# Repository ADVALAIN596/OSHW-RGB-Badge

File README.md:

# OSHW-RGB-Badge
Learn to Solder Badge with RGB-LED and [OSHW (Open Source Hardware)](http://www.oshwa.org/open-source-hardware-logo/) Design.

* RGB-LED with built-in blink/fade automatic
* Power Supply: CR2032 (3V) / LIR2032 (3.6V) cell battery
* Open-Source and released under the [Creative Commons Attribution Share-Alike License](https://creativecommons.org/licenses/by-sa/4.0/).
* **[Documentation on learn.watterott.com](https://learn.watterott.com)**

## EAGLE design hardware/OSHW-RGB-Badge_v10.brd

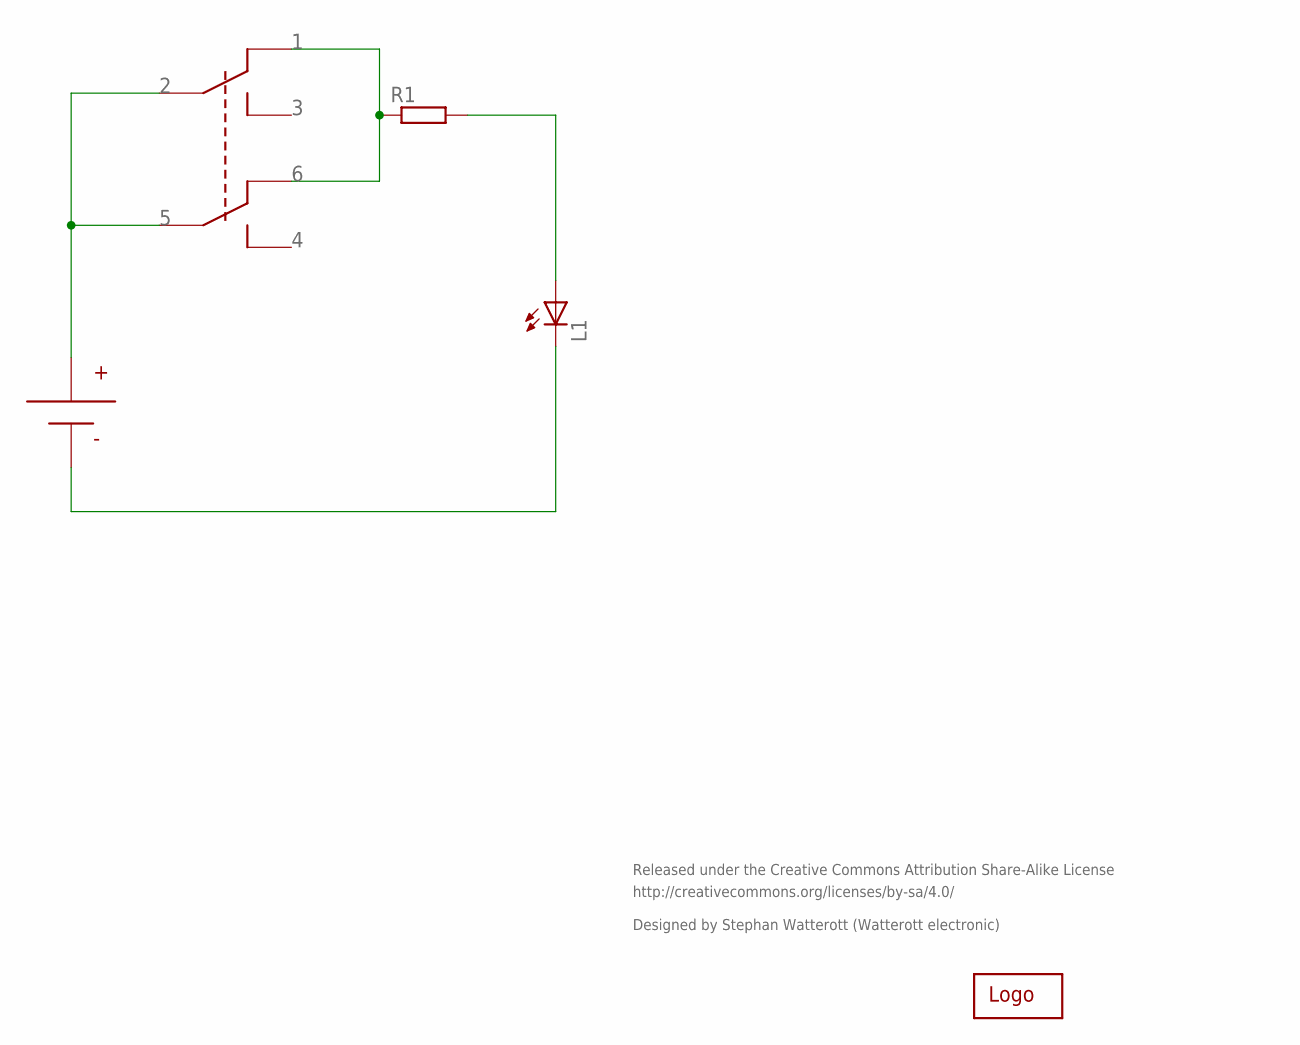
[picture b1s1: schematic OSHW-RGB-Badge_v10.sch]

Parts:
L1: LED10MM
LOGO1: LOGOPLACE; LOGO_TPLACE
R1: R-EU_0207/7; 0207/7
SW: SWITCH_6-POL_RM2.54; SWITCH_6POL_RM2.54
U$1: CN2032_BATTERY_HOLDER

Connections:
unnamed: R1.1, SW.P$1, SW.P$6
unnamed: SW.P$2, SW.P$5, U$1.P$1 (+)
unnamed: L1.A, R1.2
unnamed: L1.K (C), U$1.P$2 (-)

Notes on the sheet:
Released under the Creative Commons Attribution Share-Alike License
http://creativecommons.org/licenses/by-sa/4.0/
Designed by Stephan Watterott (Watterott electronic)

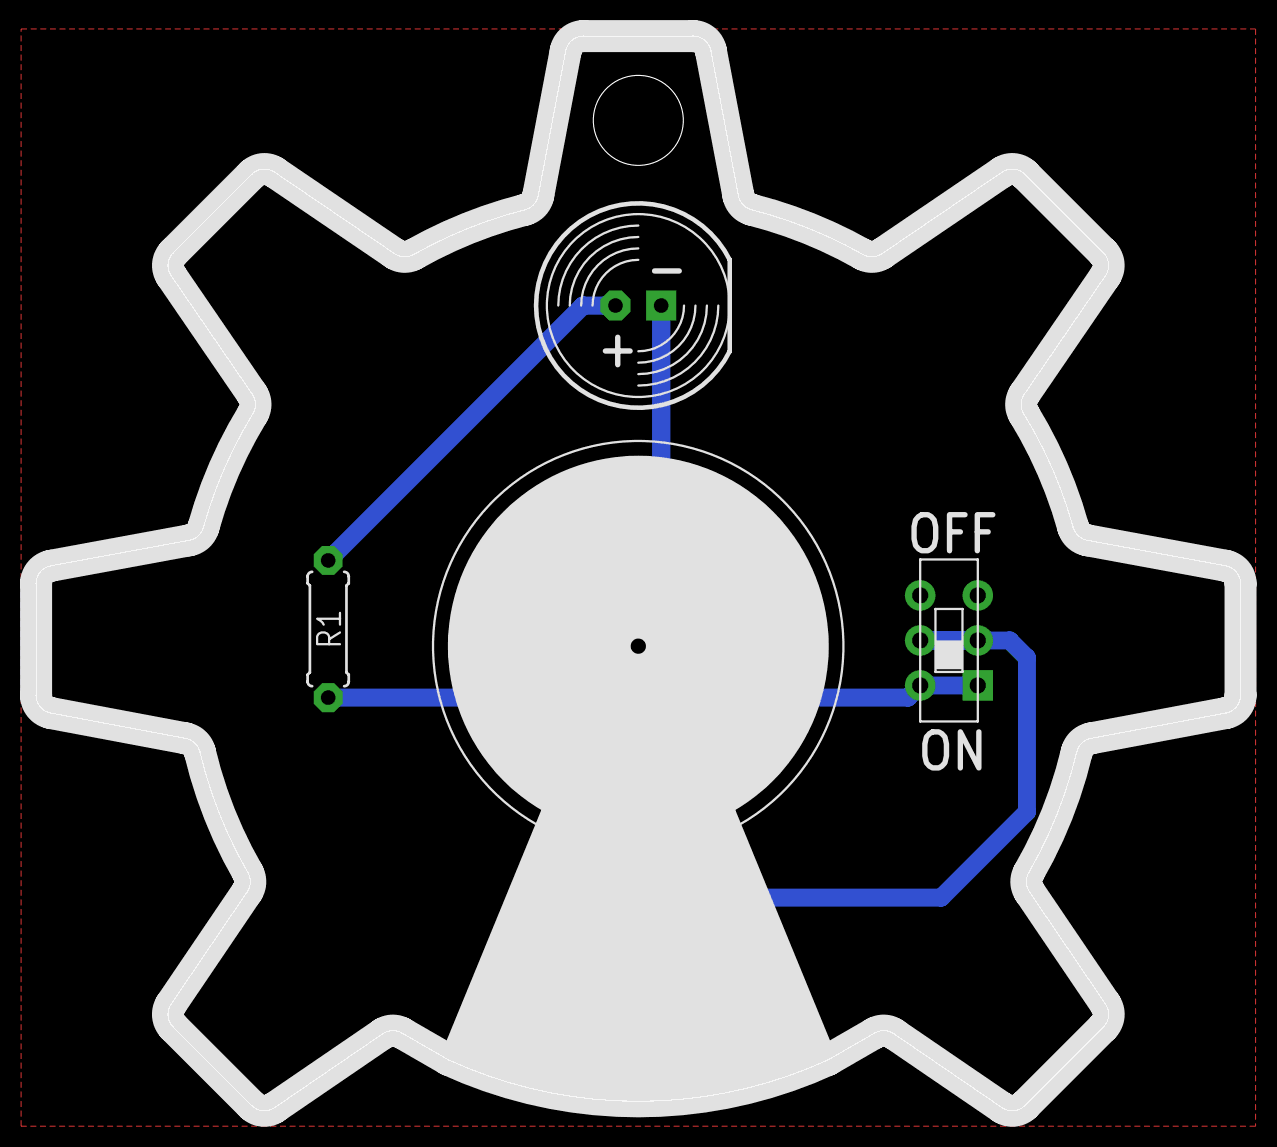
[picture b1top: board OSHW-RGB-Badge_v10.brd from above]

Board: 2 copper layers, 66.9 x 59.7 mm, 5 parts (1 on the bottom side), 4 nets.

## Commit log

2018-01-30 moved files
